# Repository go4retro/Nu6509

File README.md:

# Nu6509
MOS 6502 to MOS 6509 Adapter

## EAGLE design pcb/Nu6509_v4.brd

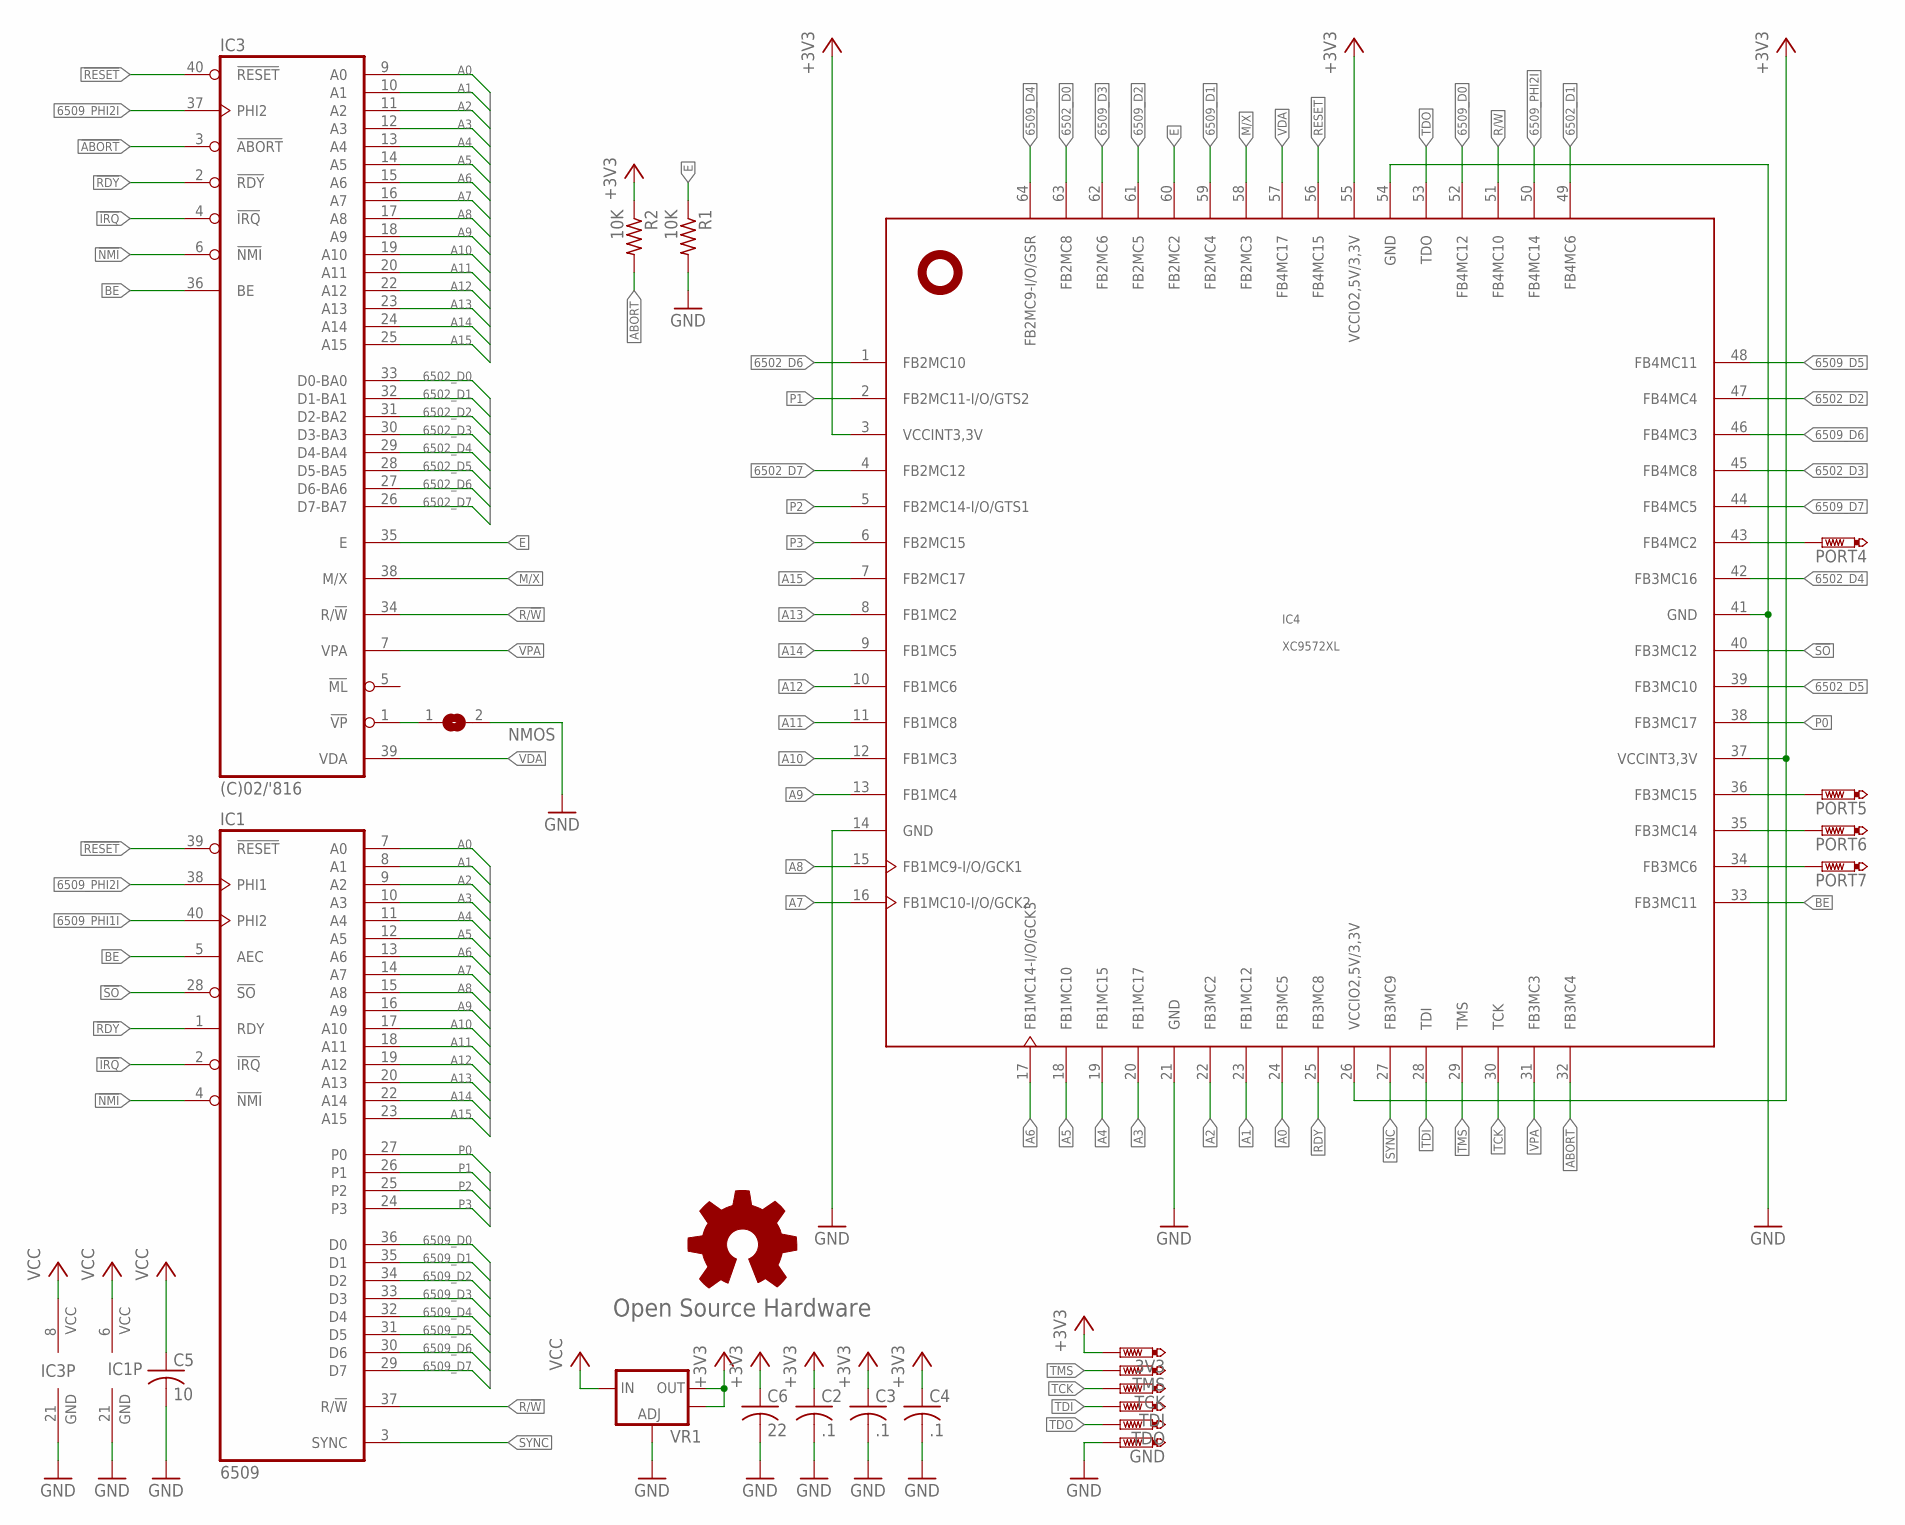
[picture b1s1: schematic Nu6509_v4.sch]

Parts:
3V3: PTR1TP08R; TP08R
C2, C3, C4: .1; C0402
C5: 10; C0805
C6: 22; C0805
GND: PTR1TP08R; TP08R
GOLD_ORB_SM1: Open Source Hardware; OSHW_5MM
IC1: 6509; DIL40-ROUNDPAD
IC3: (C)02/'816; DIL40-ROUNDPAD
IC4: XC9572XL; VQFP64
NMOS: SJ
PORT4, PORT5, PORT6, PORT7: PTR1TP08R; TP08R
R1, R2: 10K; R0402
TCK: PTR1TP08R; TP08R
TDI: PTR1TP08R; TP08R
TDO: PTR1TP08R; TP08R
TMS: PTR1TP08R; TP08R
VR1: V_REG_LM1117SOT223; SOT223

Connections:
6502_D0: IC3.33 (D0-BA0), IC4.63 (FB2MC8)
6502_D1: IC3.32 (D1-BA1), IC4.49 (FB4MC6)
6502_D2: IC3.31 (D2-BA2), IC4.47 (FB4MC4)
6502_D3: IC3.30 (D3-BA3), IC4.45 (FB4MC8)
6502_D4: IC3.29 (D4-BA4), IC4.42 (FB3MC16)
6502_D5: IC3.28 (D5-BA5), IC4.39 (FB3MC10)
6502_D6: IC3.27 (D6-BA6), IC4.1 (FB2MC10)
6502_D7: IC3.26 (D7-BA7), IC4.4 (FB2MC12)
6509_D0: IC1.36 (D0), IC4.52 (FB4MC12)
6509_D1: IC1.35 (D1), IC4.59 (FB2MC4)
6509_D2: IC1.34 (D2), IC4.61 (FB2MC5)
6509_D3: IC1.33 (D3), IC4.62 (FB2MC6)
6509_D4: IC1.32 (D4), IC4.64 (FB2MC9-I/O/GSR)
6509_D5: IC1.31 (D5), IC4.48 (FB4MC11)
6509_D6: IC1.30 (D6), IC4.46 (FB4MC3)
6509_D7: IC1.29 (D7), IC4.44 (FB4MC5)
6509_PHI1I: IC1.40 (PHI2)
6509_PHI2I: IC1.38 (PHI1), IC3.37 (PHI2), IC4.50 (FB4MC14)
!ABORT: IC3.3 (!ABORT), IC4.32 (FB3MC4), R2.2
!IRQ: IC1.2 (!IRQ), IC3.4 (!IRQ)
!NMI: IC1.4 (!NMI), IC3.6 (!NMI)
!RDY: IC1.1 (RDY), IC3.2 (!RDY), IC4.25 (FB3MC8)
!RESET: IC1.39 (!RESET), IC3.40 (!RESET), IC4.56 (FB4MC15)
!SO: IC1.28 (!SO), IC4.40 (FB3MC12)
+3V3: 3V3.TP, C2.1, C3.1, C4.1, C6.1, IC4.3 (VCCINT3,3V), IC4.26 (VCCIO2,5V/3,3V), IC4.37 (VCCINT3,3V), IC4.55 (VCCIO2,5V/3,3V), R2.1, VR1.2 (OUT), VR1.4 (OUT)
A0: IC1.7 (A0), IC3.9 (A0), IC4.24 (FB3MC5)
A1: IC1.8 (A1), IC3.10 (A1), IC4.23 (FB1MC12)
A2: IC1.9 (A2), IC3.11 (A2), IC4.22 (FB3MC2)
A3: IC1.10 (A3), IC3.12 (A3), IC4.20 (FB1MC17)
A4: IC1.11 (A4), IC3.13 (A4), IC4.19 (FB1MC15)
A5: IC1.12 (A5), IC3.14 (A5), IC4.18 (FB1MC10)
A6: IC1.13 (A6), IC3.15 (A6), IC4.17 (FB1MC14-I/O/GCK3)
A7: IC1.14 (A7), IC3.16 (A7), IC4.16 (FB1MC10-I/O/GCK2)
A8: IC1.15 (A8), IC3.17 (A8), IC4.15 (FB1MC9-I/O/GCK1)
A9: IC1.16 (A9), IC3.18 (A9), IC4.13 (FB1MC4)
A10: IC1.17 (A10), IC3.19 (A10), IC4.12 (FB1MC3)
A11: IC1.18 (A11), IC3.20 (A11), IC4.11 (FB1MC8)
A12: IC1.19 (A12), IC3.22 (A12), IC4.10 (FB1MC6)
A13: IC1.20 (A13), IC3.23 (A13), IC4.8 (FB1MC2)
A14: IC1.22 (A14), IC3.24 (A14), IC4.9 (FB1MC5)
A15: IC1.23 (A15), IC3.25 (A15), IC4.7 (FB2MC17)
BE: IC1.5 (AEC), IC3.36 (BE), IC4.33 (FB3MC11)
E: IC3.35 (E), IC4.60 (FB2MC2), R1.1
GND: C2.2, C3.2, C4.2, C5.2, C6.2, GND.TP, IC1.21 (GND), IC3.21 (GND), IC4.14 (GND), IC4.21 (GND), IC4.41 (GND), IC4.54 (GND), NMOS.2, R1.2, VR1.1 (ADJ)
M/X: IC3.38 (M/X), IC4.58 (FB2MC3)
unnamed: IC3.1 (!VP), NMOS.1
P0: IC1.27 (P0), IC4.38 (FB3MC17)
P1: IC1.26 (P1), IC4.2 (FB2MC11-I/O/GTS2)
P2: IC1.25 (P2), IC4.5 (FB2MC14-I/O/GTS1)
P3: IC1.24 (P3), IC4.6 (FB2MC15)
PORT4: IC4.43 (FB4MC2), PORT4.TP
PORT5: IC4.36 (FB3MC15), PORT5.TP
PORT6: IC4.35 (FB3MC14), PORT6.TP
PORT7: IC4.34 (FB3MC6), PORT7.TP
R/!W: IC1.37 (R/!W), IC3.34 (R/!W), IC4.51 (FB4MC10)
SYNC: IC1.3 (SYNC), IC4.27 (FB3MC9)
TCK: IC4.30 (TCK), TCK.TP
TDI: IC4.28 (TDI), TDI.TP
TDO: IC4.53 (TDO), TDO.TP
TMS: IC4.29 (TMS), TMS.TP
VCC: C5.1, IC1.6 (VCC), IC3.8 (VCC), VR1.3 (IN)
VDA: IC3.39 (VDA), IC4.57 (FB4MC17)
VPA: IC3.7 (VPA), IC4.31 (FB3MC3)

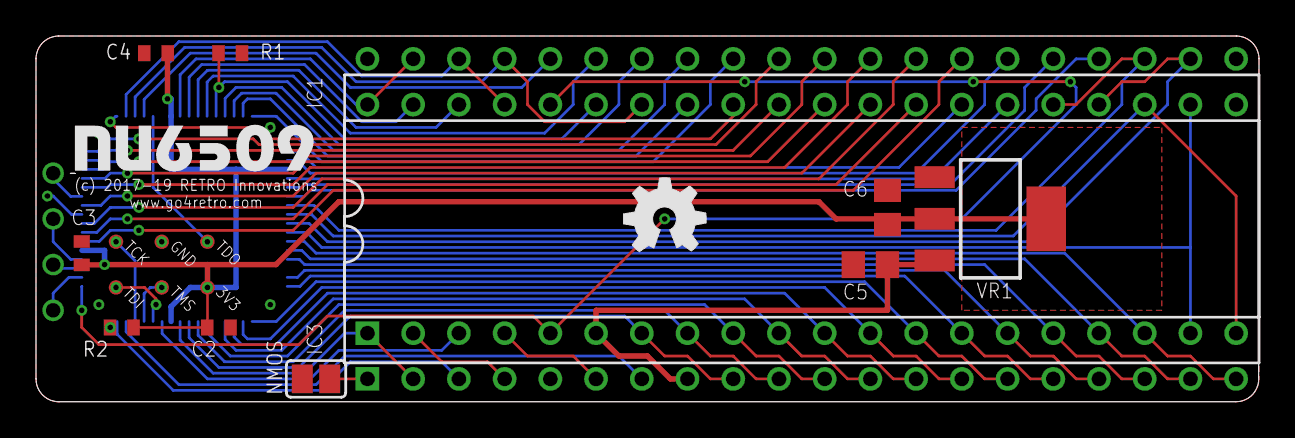
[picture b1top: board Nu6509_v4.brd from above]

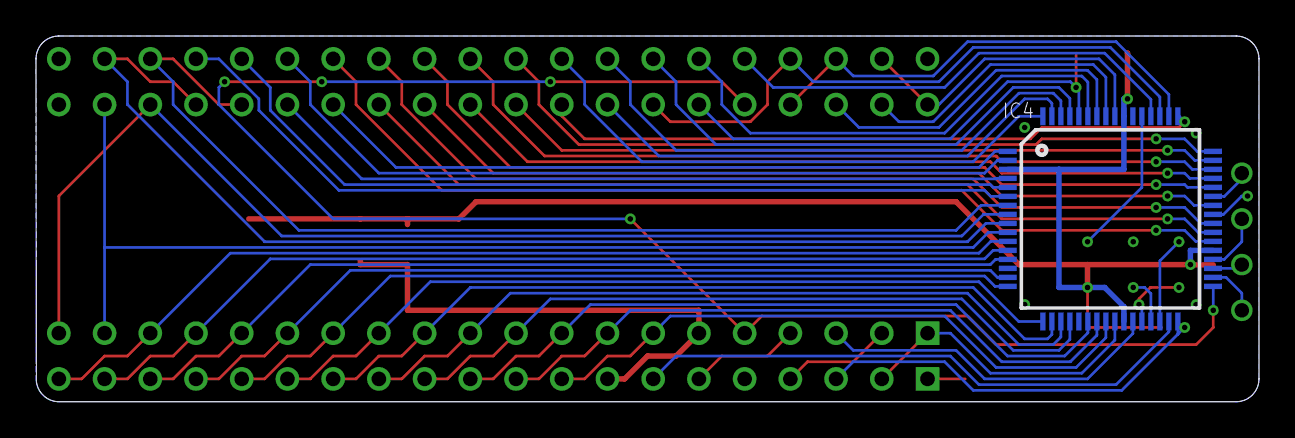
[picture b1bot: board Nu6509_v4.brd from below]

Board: 2 copper layers, 67.9 x 20.3 mm, 23 parts (5 on the bottom side), 62 nets.

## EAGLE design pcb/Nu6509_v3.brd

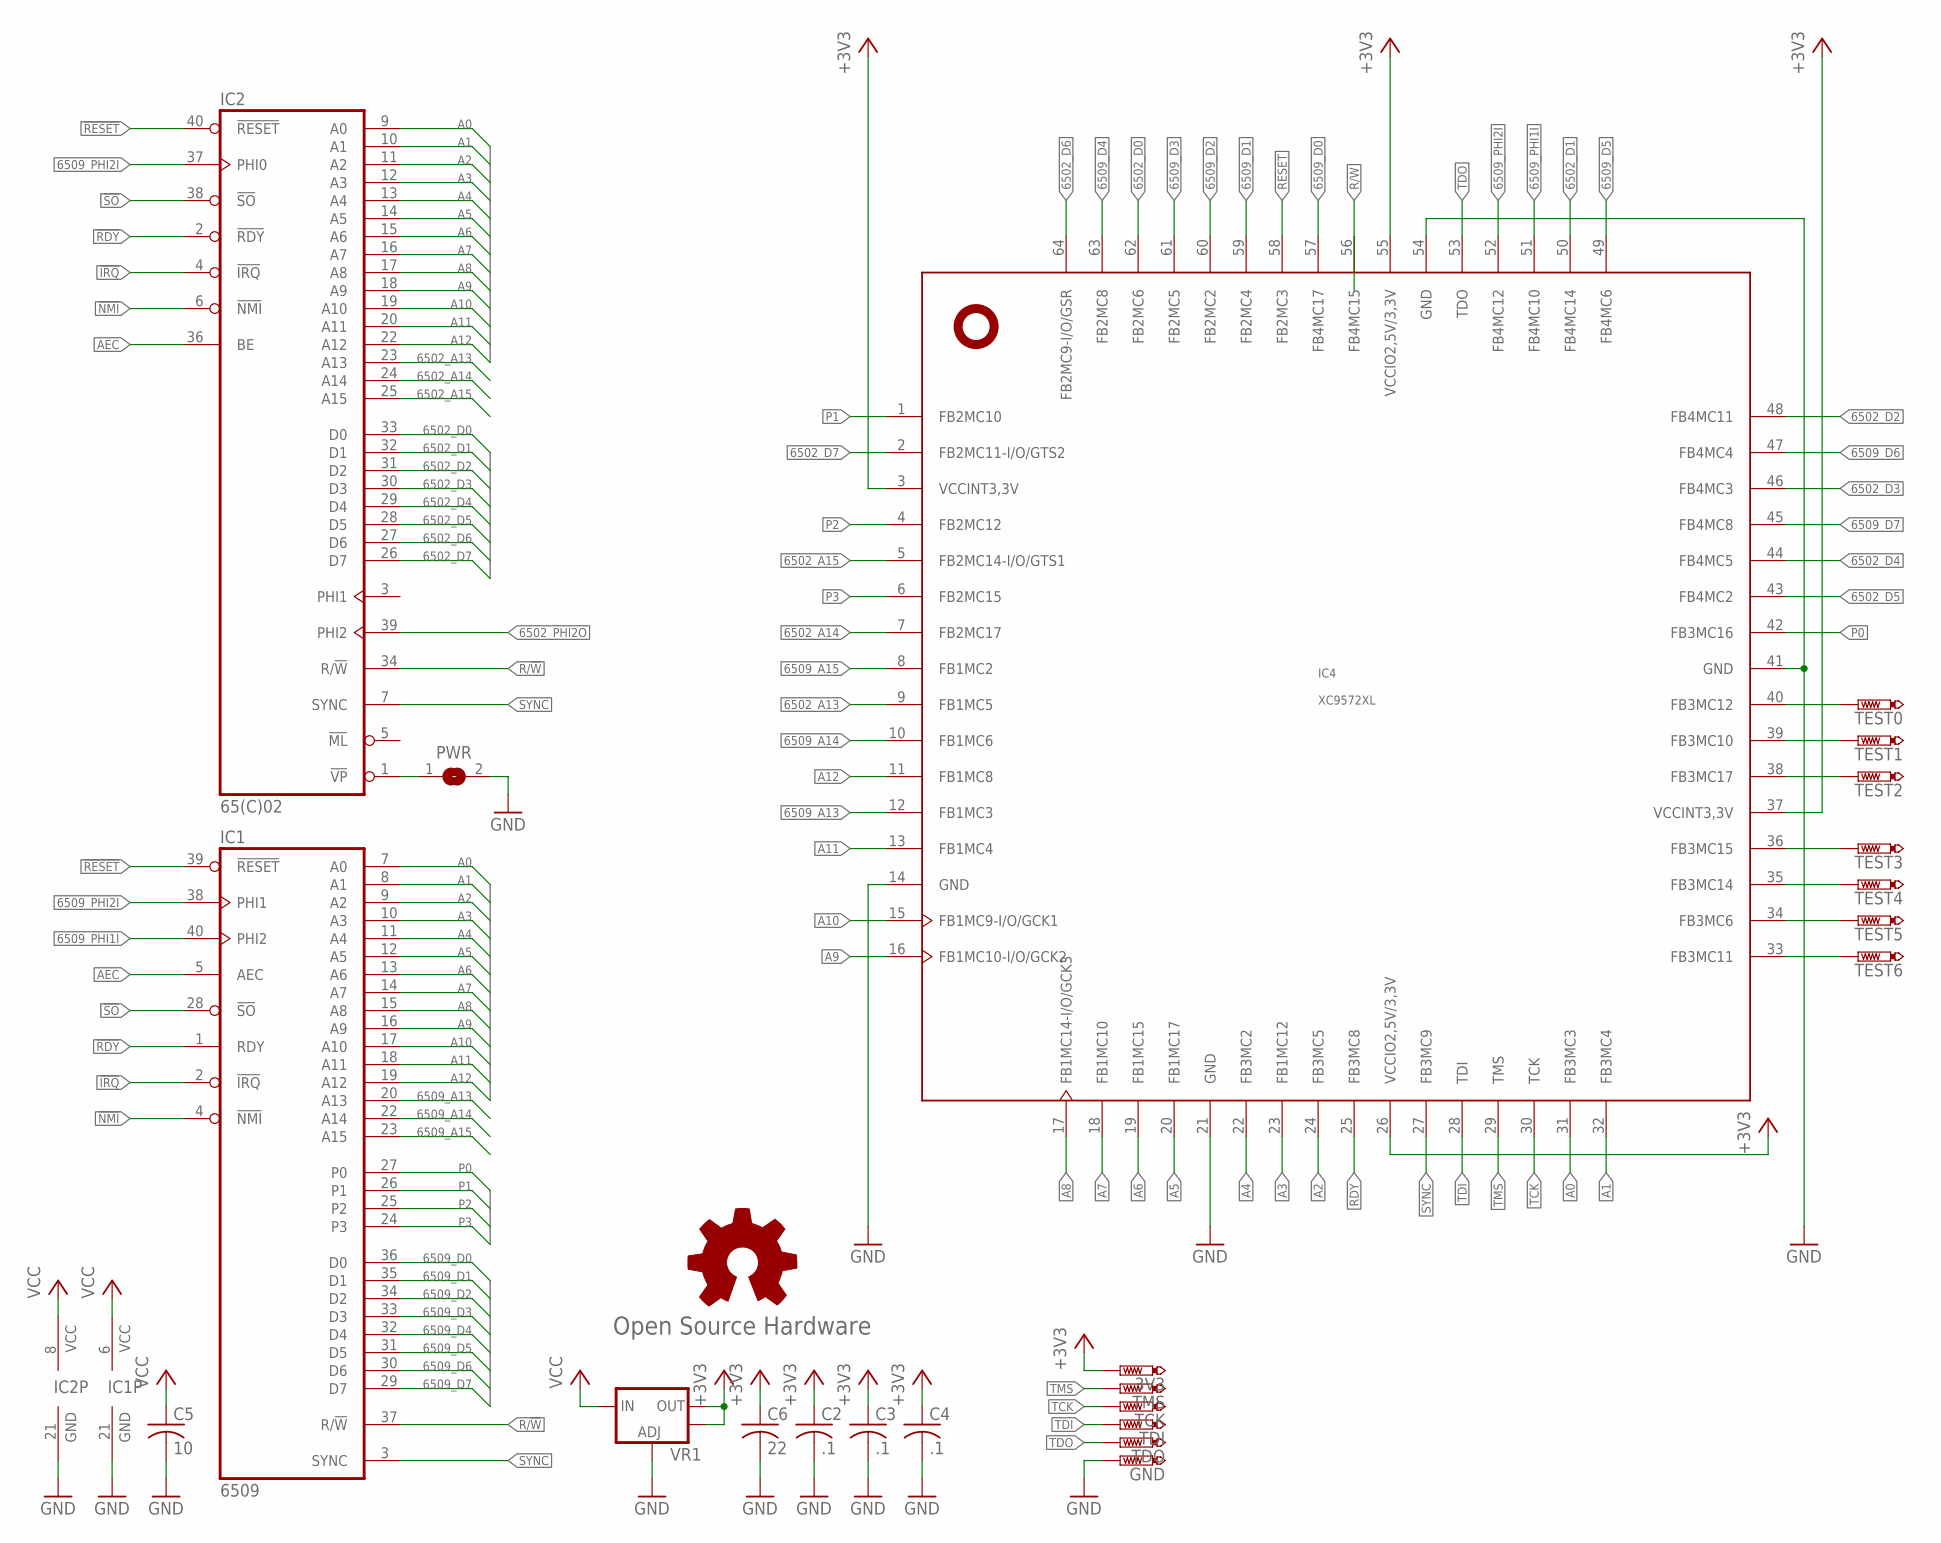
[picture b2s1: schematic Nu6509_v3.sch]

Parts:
3V3: PTR1TP08R; TP08R
C2, C3, C4: .1; C0402
C5: 10; C0805
C6: 22; C0805
GND: PTR1TP08R; TP08R
GOLD_ORB_SM1: Open Source Hardware; OSHW_5MM
IC1: 6509; DIL40-ROUNDPAD
IC2: 65(C)02; DIL40-ROUNDPAD
IC4: XC9572XL; VQFP64
PWR: SJ
TCK: PTR1TP08R; TP08R
TDI: PTR1TP08R; TP08R
TDO: PTR1TP08R; TP08R
TEST0, TEST1, TEST2, TEST3, TEST4, TEST5, TEST6: PTR1TP08R; TP08R
TMS: PTR1TP08R; TP08R
VR1: V_REG_LM1117SOT223; SOT223

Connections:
6502_A13: IC2.23 (A13), IC4.9 (FB1MC5)
6502_A14: IC2.24 (A14), IC4.7 (FB2MC17)
6502_A15: IC2.25 (A15), IC4.5 (FB2MC14-I/O/GTS1)
6502_D0: IC2.33 (D0), IC4.62 (FB2MC6)
6502_D1: IC2.32 (D1), IC4.50 (FB4MC14)
6502_D2: IC2.31 (D2), IC4.48 (FB4MC11)
6502_D3: IC2.30 (D3), IC4.46 (FB4MC3)
6502_D4: IC2.29 (D4), IC4.44 (FB4MC5)
6502_D5: IC2.28 (D5), IC4.43 (FB4MC2)
6502_D6: IC2.27 (D6), IC4.64 (FB2MC9-I/O/GSR)
6502_D7: IC2.26 (D7), IC4.2 (FB2MC11-I/O/GTS2)
6502_PHI2O: IC2.39 (PHI2)
6509_A13: IC1.20 (A13), IC4.12 (FB1MC3)
6509_A14: IC1.22 (A14), IC4.10 (FB1MC6)
6509_A15: IC1.23 (A15), IC4.8 (FB1MC2)
6509_D0: IC1.36 (D0), IC4.57 (FB4MC17)
6509_D1: IC1.35 (D1), IC4.59 (FB2MC4)
6509_D2: IC1.34 (D2), IC4.60 (FB2MC2)
6509_D3: IC1.33 (D3), IC4.61 (FB2MC5)
6509_D4: IC1.32 (D4), IC4.63 (FB2MC8)
6509_D5: IC1.31 (D5), IC4.49 (FB4MC6)
6509_D6: IC1.30 (D6), IC4.47 (FB4MC4)
6509_D7: IC1.29 (D7), IC4.45 (FB4MC8)
6509_PHI1I: IC1.40 (PHI2), IC4.51 (FB4MC10)
6509_PHI2I: IC1.38 (PHI1), IC2.37 (PHI0), IC4.52 (FB4MC12)
!IRQ: IC1.2 (!IRQ), IC2.4 (!IRQ)
!NMI: IC1.4 (!NMI), IC2.6 (!NMI)
!RDY: IC1.1 (RDY), IC2.2 (!RDY), IC4.25 (FB3MC8)
!RESET: IC1.39 (!RESET), IC2.40 (!RESET), IC4.58 (FB2MC3)
!SO: IC1.28 (!SO), IC2.38 (!SO)
+3V3: 3V3.TP, C2.1, C3.1, C4.1, C6.1, IC4.3 (VCCINT3,3V), IC4.26 (VCCIO2,5V/3,3V), IC4.37 (VCCINT3,3V), IC4.55 (VCCIO2,5V/3,3V), VR1.2 (OUT), VR1.4 (OUT)
A0: IC1.7 (A0), IC2.9 (A0), IC4.31 (FB3MC3)
A1: IC1.8 (A1), IC2.10 (A1), IC4.32 (FB3MC4)
A2: IC1.9 (A2), IC2.11 (A2), IC4.24 (FB3MC5)
A3: IC1.10 (A3), IC2.12 (A3), IC4.23 (FB1MC12)
A4: IC1.11 (A4), IC2.13 (A4), IC4.22 (FB3MC2)
A5: IC1.12 (A5), IC2.14 (A5), IC4.20 (FB1MC17)
A6: IC1.13 (A6), IC2.15 (A6), IC4.19 (FB1MC15)
A7: IC1.14 (A7), IC2.16 (A7), IC4.18 (FB1MC10)
A8: IC1.15 (A8), IC2.17 (A8), IC4.17 (FB1MC14-I/O/GCK3)
A9: IC1.16 (A9), IC2.18 (A9), IC4.16 (FB1MC10-I/O/GCK2)
A10: IC1.17 (A10), IC2.19 (A10), IC4.15 (FB1MC9-I/O/GCK1)
A11: IC1.18 (A11), IC2.20 (A11), IC4.13 (FB1MC4)
A12: IC1.19 (A12), IC2.22 (A12), IC4.11 (FB1MC8)
AEC: IC1.5 (AEC), IC2.36 (BE)
GND: C2.2, C3.2, C4.2, C5.2, C6.2, GND.TP, IC1.21 (GND), IC2.21 (GND), IC4.14 (GND), IC4.21 (GND), IC4.41 (GND), IC4.54 (GND), PWR.2, VR1.1 (ADJ)
unnamed: IC2.1 (!VP), PWR.1
P0: IC1.27 (P0), IC4.42 (FB3MC16)
P1: IC1.26 (P1), IC4.1 (FB2MC10)
P2: IC1.25 (P2), IC4.4 (FB2MC12)
P3: IC1.24 (P3), IC4.6 (FB2MC15)
R/!W: IC1.37 (R/!W), IC2.34 (R/!W), IC4.56 (FB4MC15)
SYNC: IC1.3 (SYNC), IC2.7 (SYNC), IC4.27 (FB3MC9)
TCK: IC4.30 (TCK), TCK.TP
TDI: IC4.28 (TDI), TDI.TP
TDO: IC4.53 (TDO), TDO.TP
TEST0: IC4.40 (FB3MC12), TEST0.TP
TEST1: IC4.39 (FB3MC10), TEST1.TP
TEST2: IC4.38 (FB3MC17), TEST2.TP
TEST3: IC4.36 (FB3MC15), TEST3.TP
TEST4: IC4.35 (FB3MC14), TEST4.TP
TEST5: IC4.34 (FB3MC6), TEST5.TP
TEST6: IC4.33 (FB3MC11), TEST6.TP
TMS: IC4.29 (TMS), TMS.TP
VCC: C5.1, IC1.6 (VCC), IC2.8 (VCC), VR1.3 (IN)

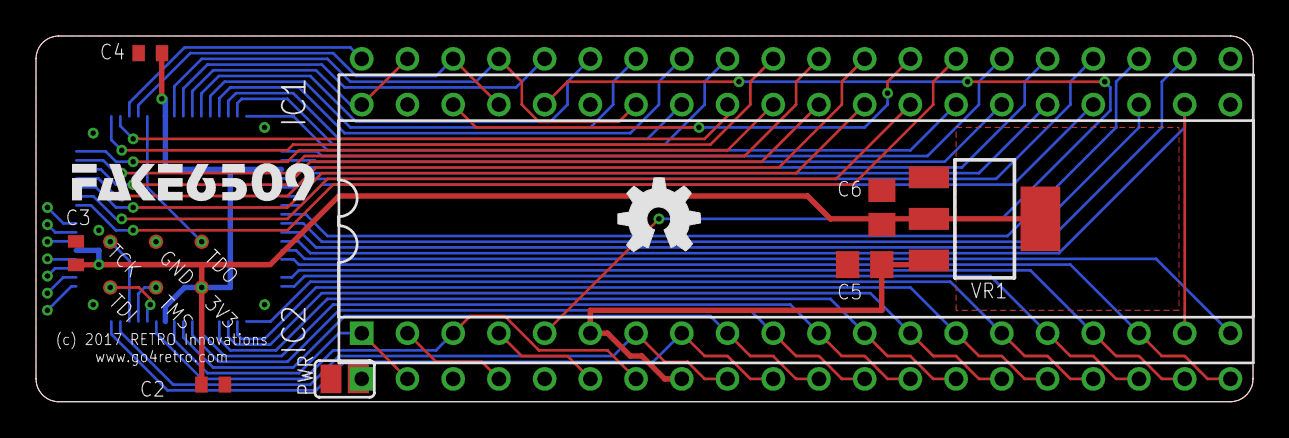
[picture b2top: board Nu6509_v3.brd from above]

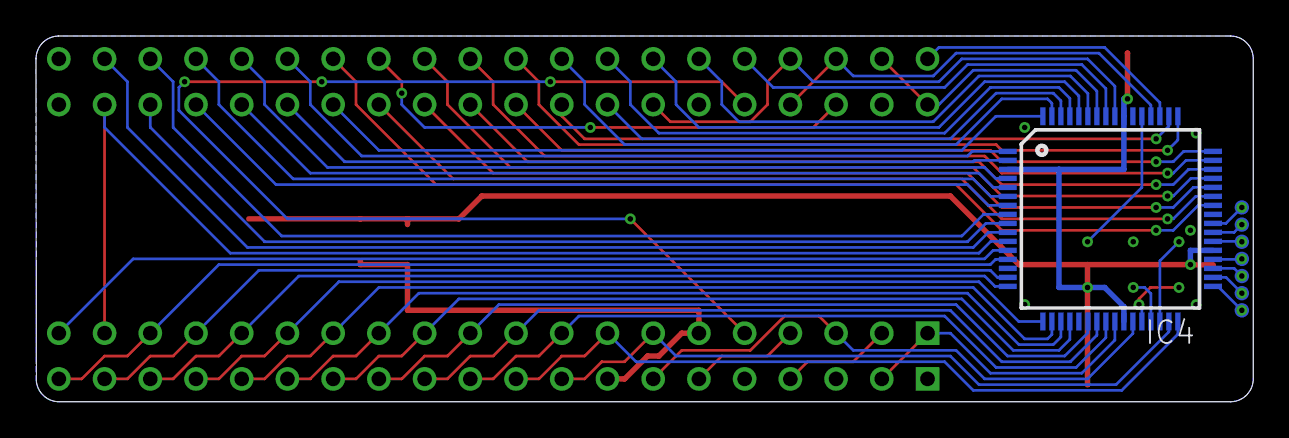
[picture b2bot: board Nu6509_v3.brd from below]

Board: 2 copper layers, 67.6 x 20.3 mm, 24 parts (8 on the bottom side), 64 nets.

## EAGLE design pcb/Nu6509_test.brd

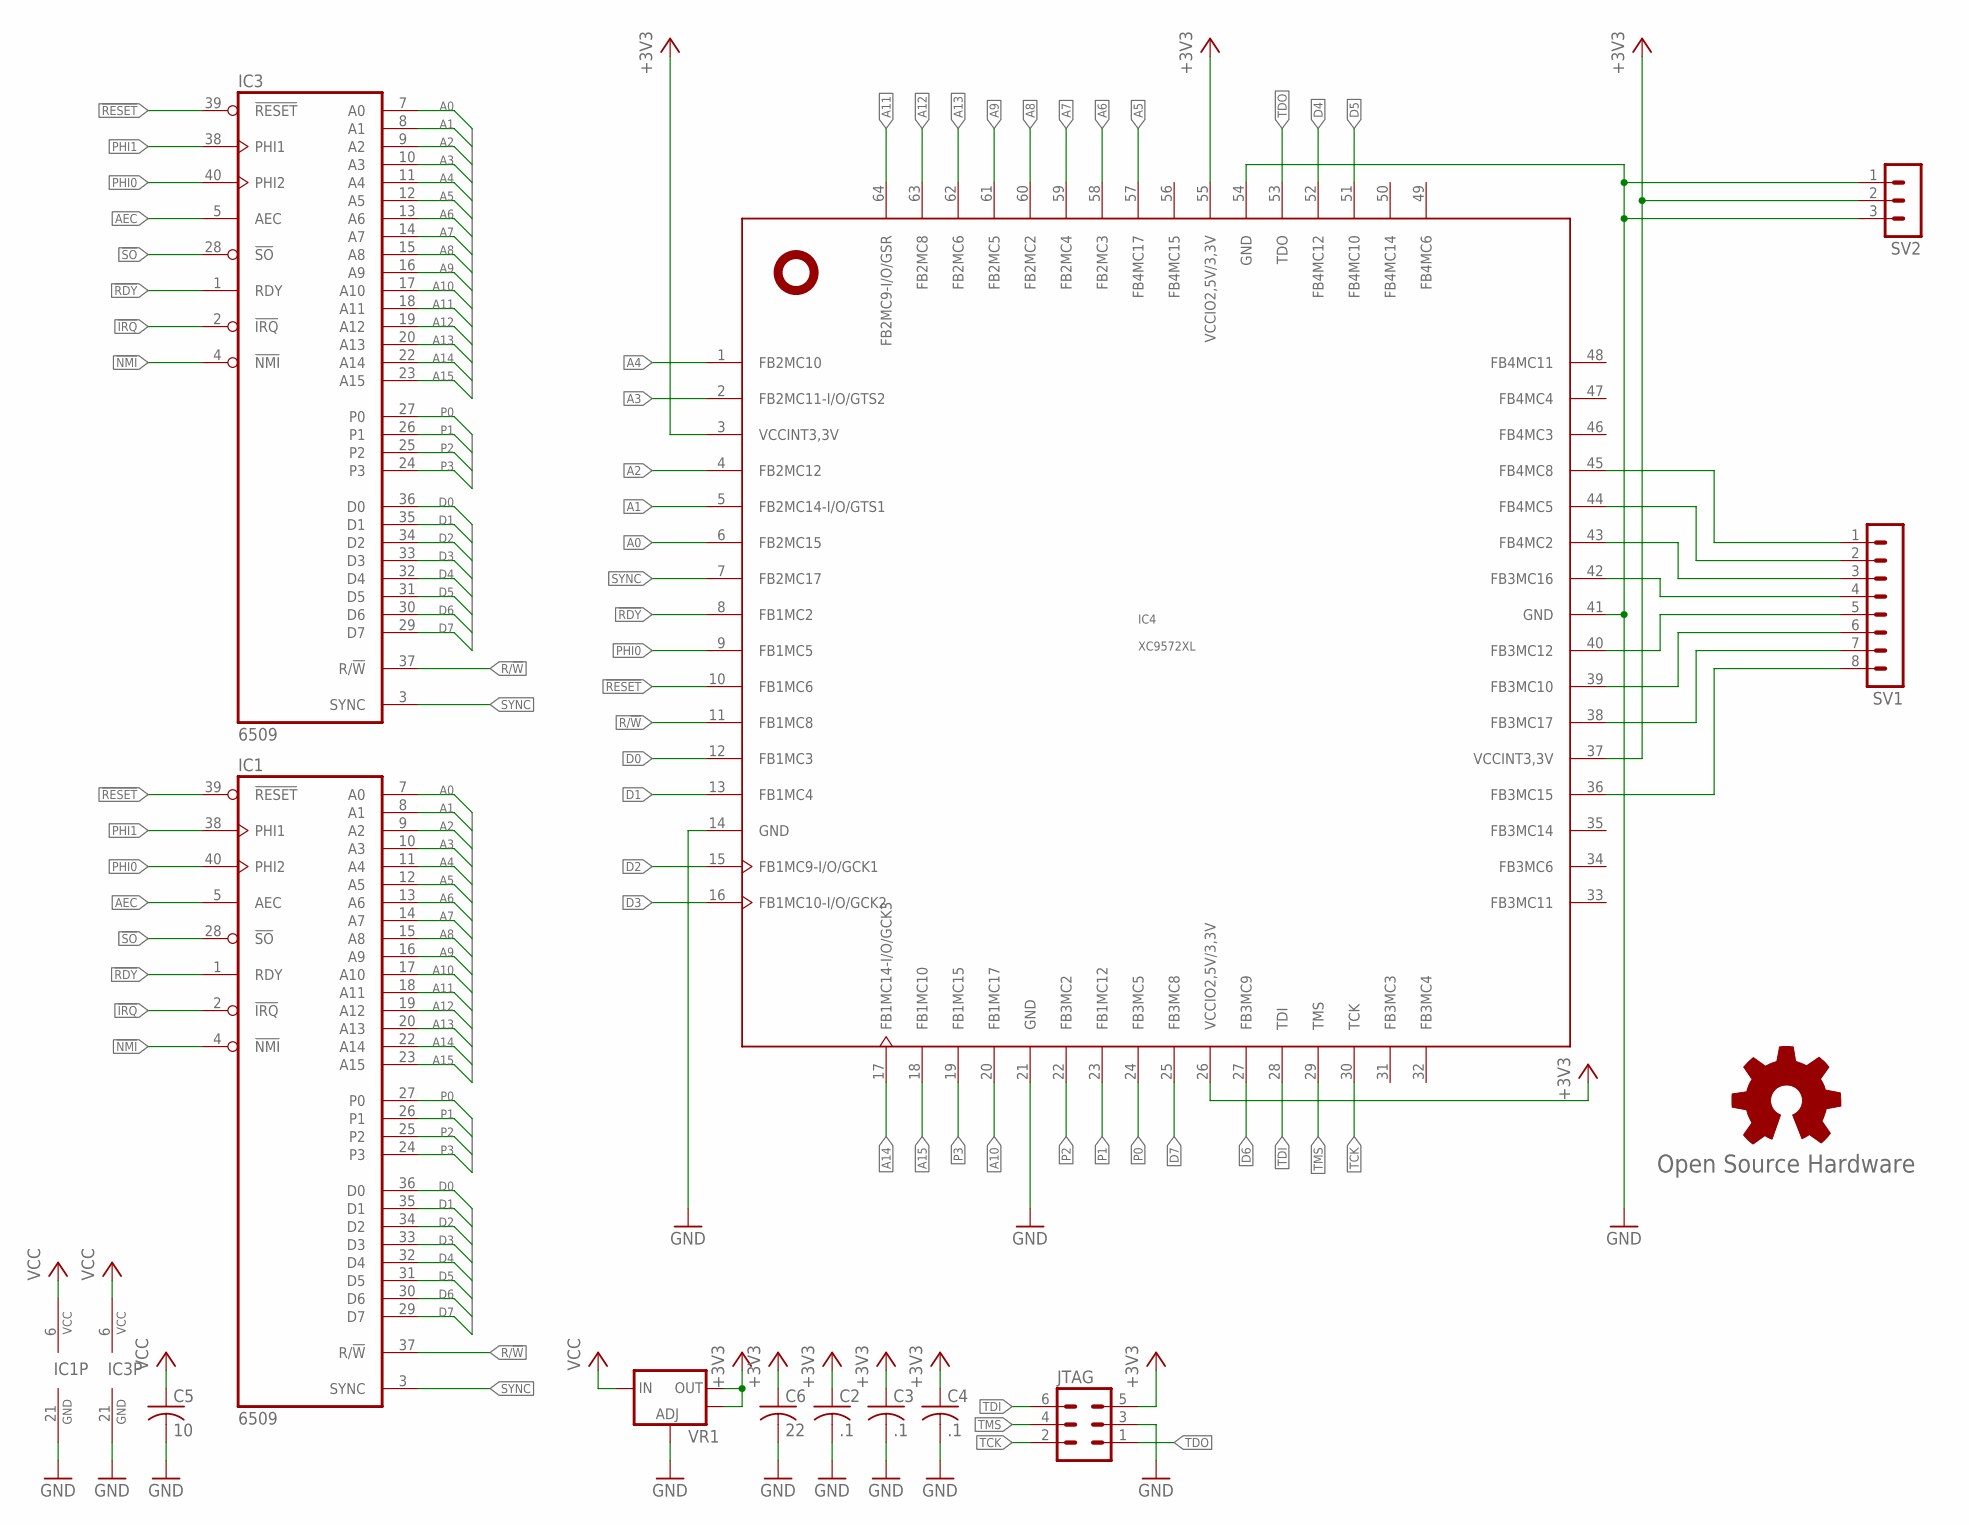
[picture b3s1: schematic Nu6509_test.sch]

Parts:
C2, C3, C4: .1; C0402
C5: 10; C0805
C6: 22; C0805
GOLD_ORB_SM1: Open Source Hardware; OSHW_5MM
IC1, IC3: 6509; DIL40-ROUNDPAD
IC4: XC9572XL; VQFP64
JTAG: MA03-2
SV1: MA08-1
SV2: MA03-1
VR1: V_REG_LM1117SOT223; SOT223

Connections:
!IRQ: IC1.2 (!IRQ), IC3.2 (!IRQ)
!NMI: IC1.4 (!NMI), IC3.4 (!NMI)
!RDY: IC1.1 (RDY), IC3.1 (RDY), IC4.8 (FB1MC2)
!RESET: IC1.39 (!RESET), IC3.39 (!RESET), IC4.10 (FB1MC6)
!SO: IC1.28 (!SO), IC3.28 (!SO)
+3V3: C2.1, C3.1, C4.1, C6.1, IC4.3 (VCCINT3,3V), IC4.26 (VCCIO2,5V/3,3V), IC4.37 (VCCINT3,3V), IC4.55 (VCCIO2,5V/3,3V), JTAG.5, SV2.2, VR1.2 (OUT), VR1.4 (OUT)
A0: IC1.7 (A0), IC3.7 (A0), IC4.6 (FB2MC15)
A1: IC1.8 (A1), IC3.8 (A1), IC4.5 (FB2MC14-I/O/GTS1)
A2: IC1.9 (A2), IC3.9 (A2), IC4.4 (FB2MC12)
A3: IC1.10 (A3), IC3.10 (A3), IC4.2 (FB2MC11-I/O/GTS2)
A4: IC1.11 (A4), IC3.11 (A4), IC4.1 (FB2MC10)
A5: IC1.12 (A5), IC3.12 (A5), IC4.57 (FB4MC17)
A6: IC1.13 (A6), IC3.13 (A6), IC4.58 (FB2MC3)
A7: IC1.14 (A7), IC3.14 (A7), IC4.59 (FB2MC4)
A8: IC1.15 (A8), IC3.15 (A8), IC4.60 (FB2MC2)
A9: IC1.16 (A9), IC3.16 (A9), IC4.61 (FB2MC5)
A10: IC1.17 (A10), IC3.17 (A10), IC4.20 (FB1MC17)
A11: IC1.18 (A11), IC3.18 (A11), IC4.64 (FB2MC9-I/O/GSR)
A12: IC1.19 (A12), IC3.19 (A12), IC4.63 (FB2MC8)
A13: IC1.20 (A13), IC3.20 (A13), IC4.62 (FB2MC6)
A14: IC1.22 (A14), IC3.22 (A14), IC4.17 (FB1MC14-I/O/GCK3)
A15: IC1.23 (A15), IC3.23 (A15), IC4.18 (FB1MC10)
AEC: IC1.5 (AEC), IC3.5 (AEC)
D0: IC1.36 (D0), IC3.36 (D0), IC4.12 (FB1MC3)
D1: IC1.35 (D1), IC3.35 (D1), IC4.13 (FB1MC4)
D2: IC1.34 (D2), IC3.34 (D2), IC4.15 (FB1MC9-I/O/GCK1)
D3: IC1.33 (D3), IC3.33 (D3), IC4.16 (FB1MC10-I/O/GCK2)
D4: IC1.32 (D4), IC3.32 (D4), IC4.52 (FB4MC12)
D5: IC1.31 (D5), IC3.31 (D5), IC4.51 (FB4MC10)
D6: IC1.30 (D6), IC3.30 (D6), IC4.27 (FB3MC9)
D7: IC1.29 (D7), IC3.29 (D7), IC4.25 (FB3MC8)
GND: C2.2, C3.2, C4.2, C5.2, C6.2, IC1.21 (GND), IC3.21 (GND), IC4.14 (GND), IC4.21 (GND), IC4.41 (GND), IC4.54 (GND), JTAG.3, SV2.1, SV2.3, VR1.1 (ADJ)
unnamed: IC4.40 (FB3MC12), SV1.5
unnamed: IC4.42 (FB3MC16), SV1.4
unnamed: IC4.43 (FB4MC2), SV1.3
unnamed: IC4.44 (FB4MC5), SV1.2
unnamed: IC4.45 (FB4MC8), SV1.1
unnamed: IC4.39 (FB3MC10), SV1.6
unnamed: IC4.38 (FB3MC17), SV1.7
unnamed: IC4.36 (FB3MC15), SV1.8
P0: IC1.27 (P0), IC3.27 (P0), IC4.24 (FB3MC5)
P1: IC1.26 (P1), IC3.26 (P1), IC4.23 (FB1MC12)
P2: IC1.25 (P2), IC3.25 (P2), IC4.22 (FB3MC2)
P3: IC1.24 (P3), IC3.24 (P3), IC4.19 (FB1MC15)
PHI0: IC1.40 (PHI2), IC3.40 (PHI2), IC4.9 (FB1MC5)
PHI1: IC1.38 (PHI1), IC3.38 (PHI1)
R/!W: IC1.37 (R/!W), IC3.37 (R/!W), IC4.11 (FB1MC8)
SYNC: IC1.3 (SYNC), IC3.3 (SYNC), IC4.7 (FB2MC17)
TCK: IC4.30 (TCK), JTAG.2
TDI: IC4.28 (TDI), JTAG.6
TDO: IC4.53 (TDO), JTAG.1
TMS: IC4.29 (TMS), JTAG.4
VCC: C5.1, IC1.6 (VCC), IC3.6 (VCC), VR1.3 (IN)

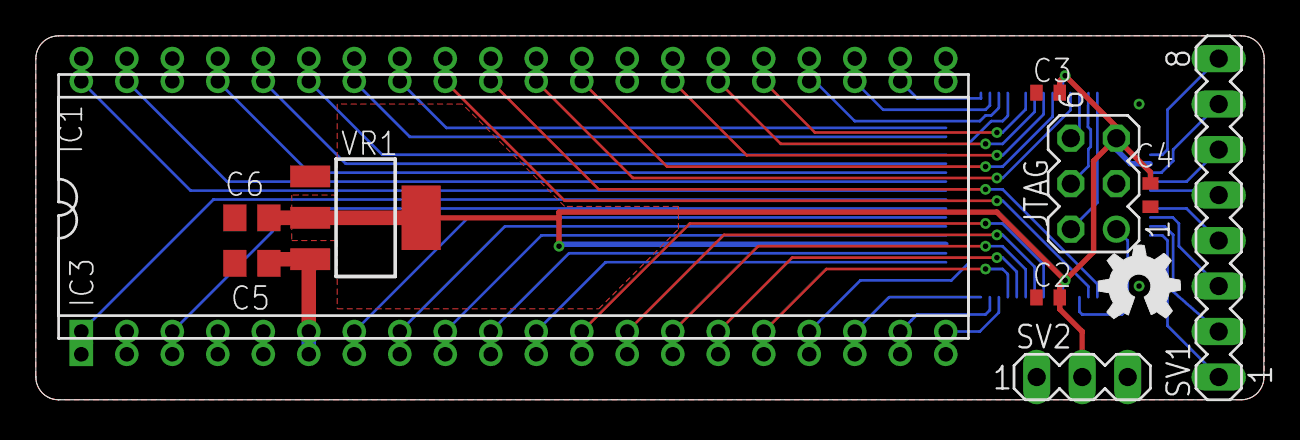
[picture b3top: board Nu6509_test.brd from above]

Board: 2 copper layers, 68.6 x 20.3 mm, 13 parts (1 on the bottom side), 53 nets.

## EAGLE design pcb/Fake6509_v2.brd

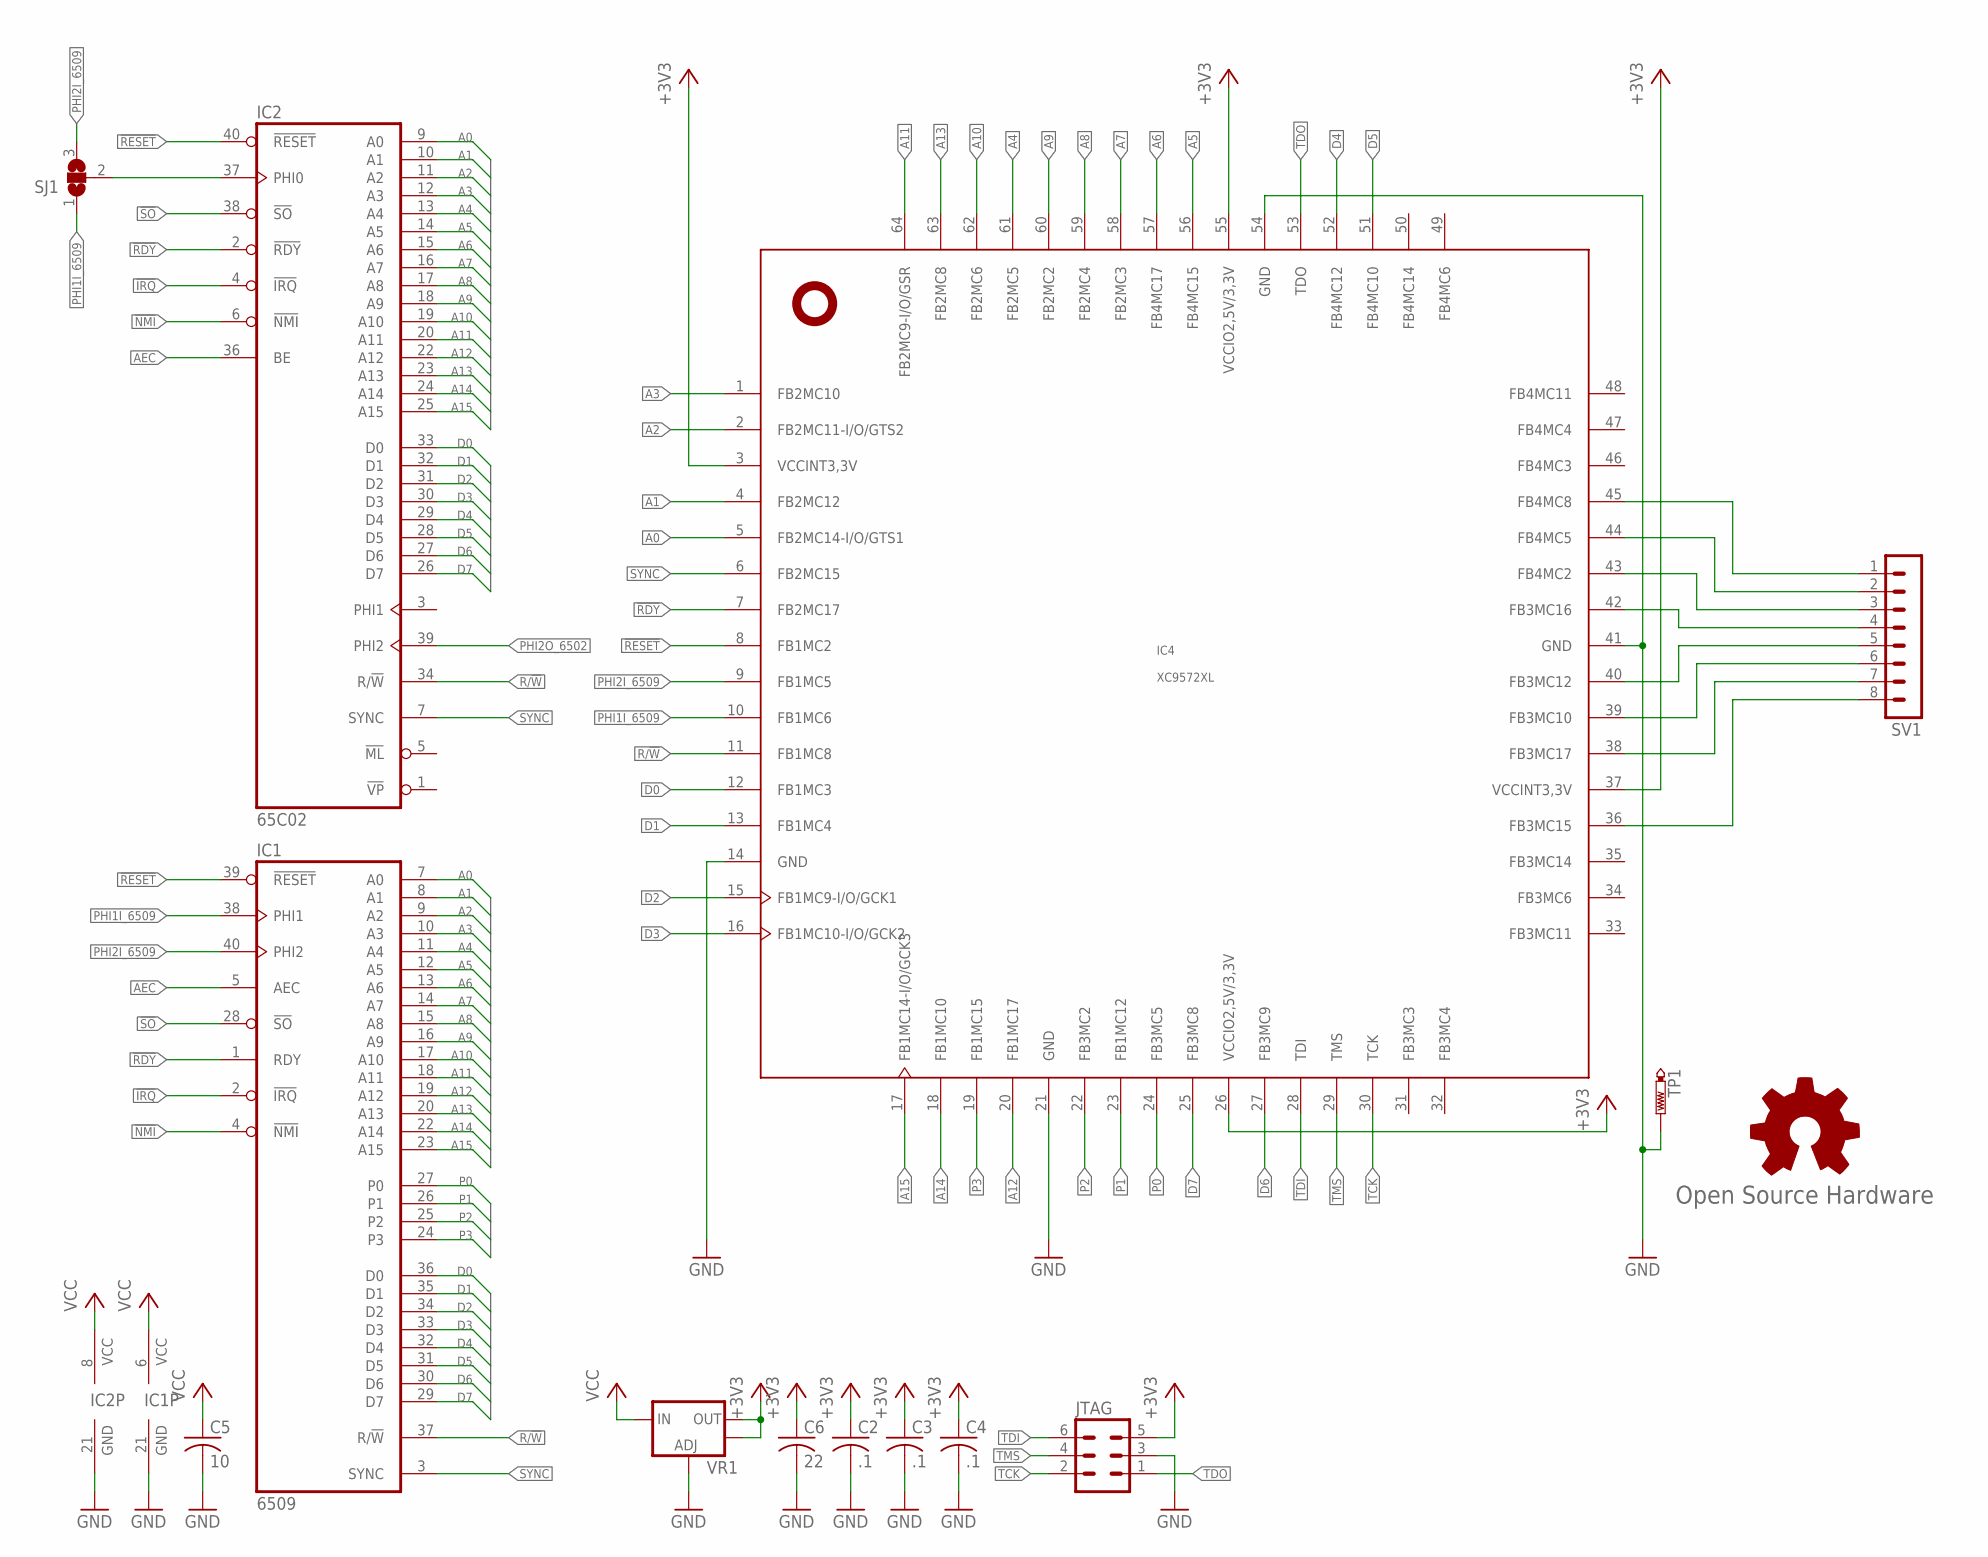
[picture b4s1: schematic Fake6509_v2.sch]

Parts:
C2, C3, C4: .1; C0402
C5: 10; C0805
C6: 22; C0805
GOLD_ORB_SM1: Open Source Hardware; OSHW_5MM
IC1: 6509; DIL40-ROUNDPAD
IC2: 65C02; DIL40-ROUNDPAD
IC4: XC9572XL; VQFP64
JTAG: MA03-2
SJ1: SJ2W; SJ_2
SV1: MA08-1
TP1: PTR1B1,27; B1,27
VR1: V_REG_LM1117SOT223; SOT223

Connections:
!IRQ: IC1.2 (!IRQ), IC2.4 (!IRQ)
!NMI: IC1.4 (!NMI), IC2.6 (!NMI)
!RDY: IC1.1 (RDY), IC2.2 (!RDY), IC4.7 (FB2MC17)
!RESET: IC1.39 (!RESET), IC2.40 (!RESET), IC4.8 (FB1MC2)
!SO: IC1.28 (!SO), IC2.38 (!SO)
+3V3: C2.1, C3.1, C4.1, C6.1, IC4.3 (VCCINT3,3V), IC4.26 (VCCIO2,5V/3,3V), IC4.37 (VCCINT3,3V), IC4.55 (VCCIO2,5V/3,3V), JTAG.5, VR1.2 (OUT), VR1.4 (OUT)
A0: IC1.7 (A0), IC2.9 (A0), IC4.5 (FB2MC14-I/O/GTS1)
A1: IC1.8 (A1), IC2.10 (A1), IC4.4 (FB2MC12)
A2: IC1.9 (A2), IC2.11 (A2), IC4.2 (FB2MC11-I/O/GTS2)
A3: IC1.10 (A3), IC2.12 (A3), IC4.1 (FB2MC10)
A4: IC1.11 (A4), IC2.13 (A4), IC4.61 (FB2MC5)
A5: IC1.12 (A5), IC2.14 (A5), IC4.56 (FB4MC15)
A6: IC1.13 (A6), IC2.15 (A6), IC4.57 (FB4MC17)
A7: IC1.14 (A7), IC2.16 (A7), IC4.58 (FB2MC3)
A8: IC1.15 (A8), IC2.17 (A8), IC4.59 (FB2MC4)
A9: IC1.16 (A9), IC2.18 (A9), IC4.60 (FB2MC2)
A10: IC1.17 (A10), IC2.19 (A10), IC4.62 (FB2MC6)
A11: IC1.18 (A11), IC2.20 (A11), IC4.64 (FB2MC9-I/O/GSR)
A12: IC1.19 (A12), IC2.22 (A12), IC4.20 (FB1MC17)
A13: IC1.20 (A13), IC2.23 (A13), IC4.63 (FB2MC8)
A14: IC1.22 (A14), IC2.24 (A14), IC4.18 (FB1MC10)
A15: IC1.23 (A15), IC2.25 (A15), IC4.17 (FB1MC14-I/O/GCK3)
AEC: IC1.5 (AEC), IC2.36 (BE)
D0: IC1.36 (D0), IC2.33 (D0), IC4.12 (FB1MC3)
D1: IC1.35 (D1), IC2.32 (D1), IC4.13 (FB1MC4)
D2: IC1.34 (D2), IC2.31 (D2), IC4.15 (FB1MC9-I/O/GCK1)
D3: IC1.33 (D3), IC2.30 (D3), IC4.16 (FB1MC10-I/O/GCK2)
D4: IC1.32 (D4), IC2.29 (D4), IC4.52 (FB4MC12)
D5: IC1.31 (D5), IC2.28 (D5), IC4.51 (FB4MC10)
D6: IC1.30 (D6), IC2.27 (D6), IC4.27 (FB3MC9)
D7: IC1.29 (D7), IC2.26 (D7), IC4.25 (FB3MC8)
GND: C2.2, C3.2, C4.2, C5.2, C6.2, IC1.21 (GND), IC2.21 (GND), IC4.14 (GND), IC4.21 (GND), IC4.41 (GND), IC4.54 (GND), JTAG.3, TP1.TP, VR1.1 (ADJ)
unnamed: IC4.40 (FB3MC12), SV1.5
unnamed: IC4.42 (FB3MC16), SV1.4
unnamed: IC4.43 (FB4MC2), SV1.3
unnamed: IC4.44 (FB4MC5), SV1.2
unnamed: IC4.45 (FB4MC8), SV1.1
unnamed: IC4.39 (FB3MC10), SV1.6
unnamed: IC4.38 (FB3MC17), SV1.7
unnamed: IC4.36 (FB3MC15), SV1.8
P0: IC1.27 (P0), IC4.24 (FB3MC5)
P1: IC1.26 (P1), IC4.23 (FB1MC12)
P2: IC1.25 (P2), IC4.22 (FB3MC2)
P3: IC1.24 (P3), IC4.19 (FB1MC15)
PHI1I_6509: IC1.38 (PHI1), IC4.10 (FB1MC6), SJ1.1
PHI2I_6502: IC2.37 (PHI0), SJ1.2
PHI2I_6509: IC1.40 (PHI2), IC4.9 (FB1MC5), SJ1.3
PHI2O_6502: IC2.39 (PHI2)
R/!W: IC1.37 (R/!W), IC2.34 (R/!W), IC4.11 (FB1MC8)
SYNC: IC1.3 (SYNC), IC2.7 (SYNC), IC4.6 (FB2MC15)
TCK: IC4.30 (TCK), JTAG.2
TDI: IC4.28 (TDI), JTAG.6
TDO: IC4.53 (TDO), JTAG.1
TMS: IC4.29 (TMS), JTAG.4
VCC: C5.1, IC1.6 (VCC), IC2.8 (VCC), VR1.3 (IN)

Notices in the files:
pcb/Fake6509_v2.brd:
(c) 2017 RETRO Innovations
pcb/Nu6509_v4.brd:
(c) 2017-19 RETRO Innovations
parts and their libraries:
SparkFun: Licensing: CC v3.0 Share-Alike You are welcome to use this library for commercial purposes.
